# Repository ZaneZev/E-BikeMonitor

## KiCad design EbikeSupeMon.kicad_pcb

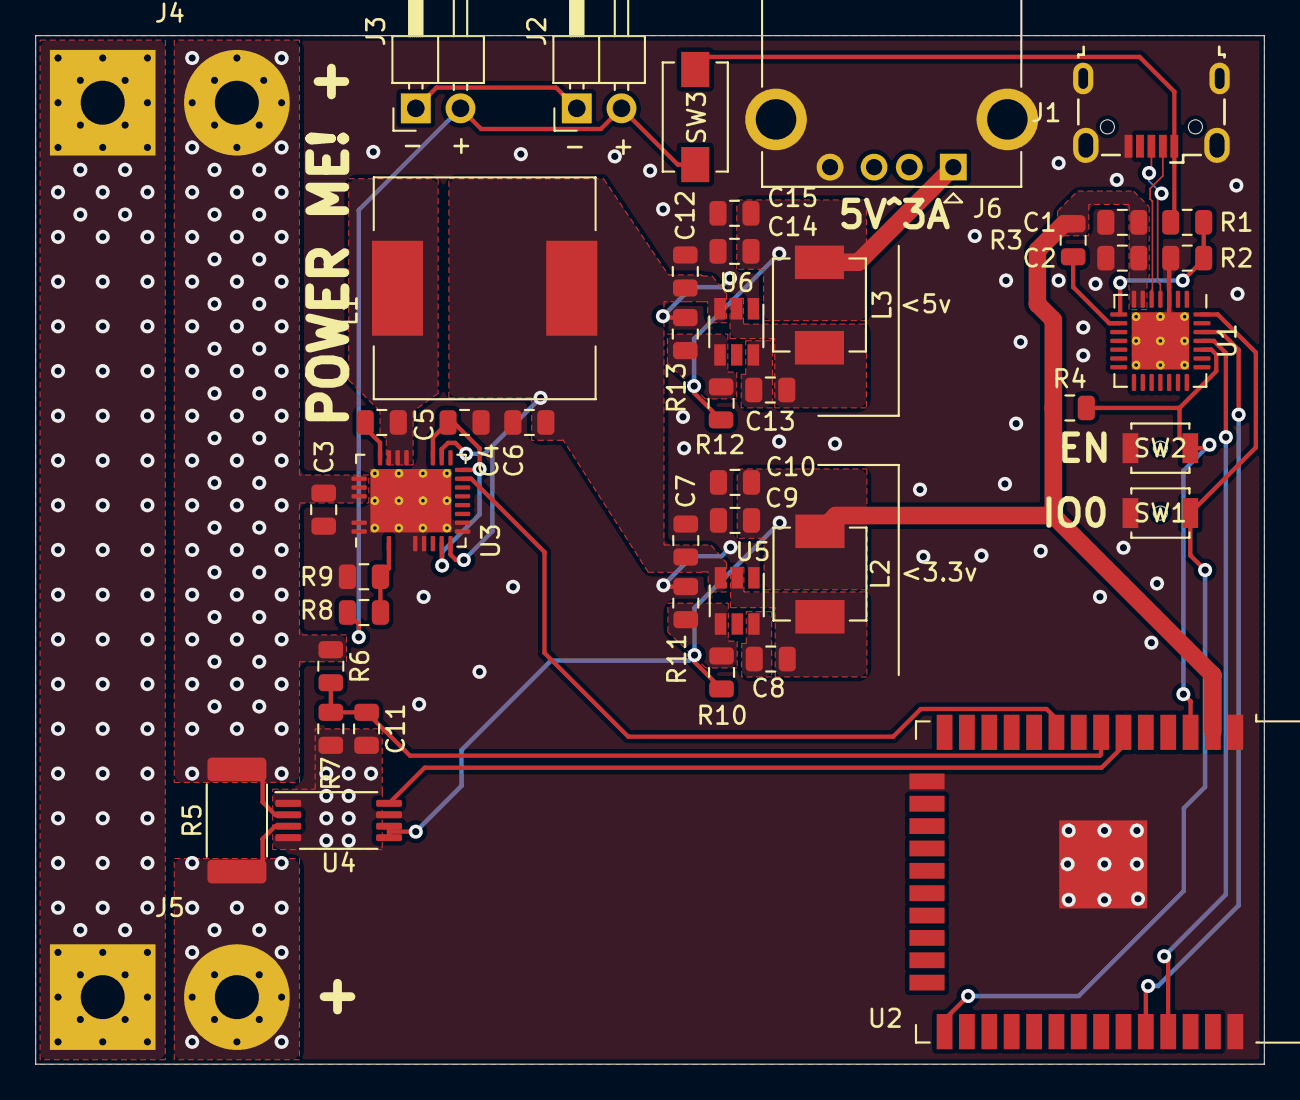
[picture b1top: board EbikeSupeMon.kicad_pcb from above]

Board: 2 copper layers, 69.8 x 58.4 mm, 46 parts (0 on the bottom side), 30 nets.

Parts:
C1: 4.7uF X5R; C_0805_2012Metric
C2: 0.1uF X5R; C_0805_2012Metric
C3: 4.7uF 100v XR7; C_0805_2012Metric
C4: 1uF X5R 5v; C_0805_2012Metric
C5: 0.1uF 100v X7R; C_0805_2012Metric
C6: 47uF 25v X5R; C_0805_2012Metric
C7, C12: 10uF 12V; C_0805_2012Metric
C8, C13: 100nF X5R 6V; C_0805_2012Metric
C9, C10, C14, C15: 22uF X7R 10v; C_0805_2012Metric
C11: 100pF X7R 100v; C_0805_2012Metric
J1: USB_B_Micro; USB_Micro-B_Wuerth_629105150521
J2: Key switch; PinHeader_1x02_P2.54mm_Horizontal
J3: Controller enable; PinHeader_1x02_P2.54mm_Horizontal
J4: Bat IN; SolderWirePad_1x02_P7.62mm_Drill2.5mm
J5: Motor Out; SolderWirePad_1x02_P7.62mm_Drill2.5mm
J6: USB_A; USB_A_CONNFLY_DS1095-WNR0
L1: 47uH; L_Wuerth_WE-PD-Typ-LS
L2, L3: 3.3uH; L_Vishay_IHLP-2020
R1: 22.1k; R_0805_2012Metric
R2: 47.5k; R_0805_2012Metric
R3, R9: 2k; R_0805_2012Metric
R4, R7, R11, R13: 10k; R_0805_2012Metric
R5: 500u ohm 2Watts; R_2512_6332Metric
R6: 287k; R_0805_2012Metric
R8: 1k; R_0805_2012Metric
R10: 31.6k; R_0805_2012Metric
R12: 52.3k; R_0805_2012Metric
SW1: IO_0; SW_SPST_B3U-1000P-B
SW2: EN; SW_SPST_B3U-1000P-B
SW3: USB-Reg_EN; SW_SPST_EVQPE1
U1: CP2102N-QFN28; TQFN-28-1EP_5x5mm_P0.5mm_EP3.25x3.25mm_ThermalVias
U2: ESP32-WROOM-32
U3: LTC7103; QFN-36-1EP_5x6mm_P0.5mm_EP3.6x4.6mm_ThermalVias
U4: INA240A3PW; TSSOP-8_4.4x3mm_P0.65mm
U5, U6: AP62300; TSOT-23-6

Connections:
+3V3: C1.1, C2.1, C9.1, C10.1, L2.2, R3.2, R4.1, R10.1, U1.6, U1.7, U2.2, U4.5, U4.6
+5V: C14.1, C15.1, J6.1, L3.2, R12.1
+12V: C6.1, C7.1, C12.1, L1.2, U3.10, U3.20, U5.3, U6.3
/12V_I_mon: U2.9, U3.17
/BattVRead: C11.1, R6.2, R7.1, U2.7
/D+: J1.3, U1.4
/D-: J1.2, U1.5
/DTR: SW1.2, U1.28, U2.25
/EN: R4.2, SW2.2, U1.24, U2.3
/EN-5v: J2.2, J3.2, R8.2, SW3.2
/Isense: U2.6, U4.8
/RXD0: U1.26, U2.34
/Sheet5F3EA405/VBatt: C3.1, J4.2, R5.1, R5.2, R6.1, U3.30, U3.31, U3.32, U4.2
/TXD0: U1.25, U2.35
GND: C1.2, C2.2, C3.2, C4.2, C6.2, C7.2, C9.2, C10.2, C11.2, C12.2, C14.2, C15.2, J1.5, J1.6, J4.1, J5.1, J6.4, J6.5, R2.2, R7.2, R9.1, R11.2, R13.2, SW1.1, SW2.1, U1.3, U1.29, U2.1, U2.15, U2.38, U2.39, U3.6, U3.7, U3.11, U3.12, U3.35, U3.36, U3.37, U4.1, U4.4, U4.7, U5.1, U6.1
unnamed: C4.1, U3.9, U3.18, U3.21
unnamed: C5.1, U3.27
unnamed: C5.2, L1.1, U3.24, U3.25, U3.26
unnamed: C8.1, U5.6
unnamed: C8.2, L2.1, U5.2
unnamed: C13.1, U6.6
unnamed: C13.2, L3.1, U6.2
unnamed: J2.1, J3.1
unnamed: J5.2, R5.3, R5.4, U4.3
unnamed: R1.1, R2.1, U1.8
unnamed: R3.1, U1.9
unnamed: R8.1, R9.2, U3.3
unnamed: R10.2, R11.1, U5.4
unnamed: R12.2, R13.1, U6.4
VBUS: J1.1, R1.2, SW3.1

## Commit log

2020-08-14 init commit
2020-08-14 git ignore added
2020-08-24 micro support todo
2020-08-25 finishing up schimatic
2020-08-31 push before branch
2020-08-31 BattV to 12 Regg added
2020-09-01 cascading regulators done
2020-09-01 Time for layout!
2020-09-02 5v +3.3v reg layed out
2020-09-02 12vReg done
2020-09-02 layout proper started
2020-09-02 rev 2 done
2020-09-14 V1 done
2020-09-14 Revert "V1 done"
    This reverts commit a77a7909c44a712f8c8e294f96d6a3631c4105b5.
2020-09-14 Go 2 is a go!
2020-09-14 2 12v reg v
2020-09-14 2 12v reg v
    (cherry picked from commit e80781844bee15763a75ec210b83760850c4e868)
2020-09-14 Revert "2 12v reg v"
    This reverts commit 039d006401861a5917fcf1b07647dbdfad4f578a.
